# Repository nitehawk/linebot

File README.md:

linebot
=======

Simple Line following robot

This design is based on a design at http://playwithrobots.com/make-it-form-scratch/simple-line-follower-robot
I have switched the sensor modules to use IR LEDs and IR Photodiodes instead of basic white LEDs.
Schematics capture was originally done in KiCad.   Rebuilt as v2 in diptrace.

Boards can be ordered from OshPark:
v1 board: http://www.oshpark.com/shared_projects/IUjxxEeG
v2 main board:  http://www.oshpark.com/shared_projects/y54Hc1CZ
v2 sensor board:  http://www.oshpark.com/shared_projects/1NccGd6E

I will be developing a model for the chassis for the v1 electronics printable in a 3D printer.

Status:
========

I have ordered a set of v1 electronics from Oshpark.   Chassis design will start after the boards and parts arrive and are tested.

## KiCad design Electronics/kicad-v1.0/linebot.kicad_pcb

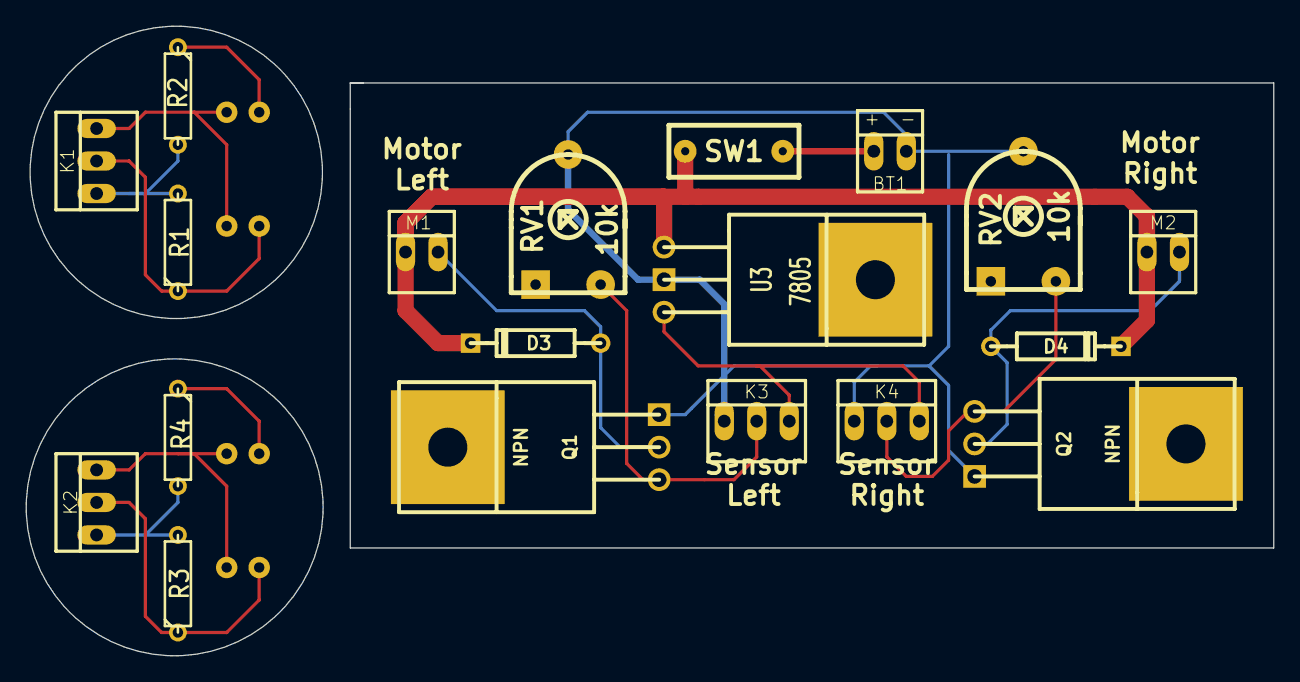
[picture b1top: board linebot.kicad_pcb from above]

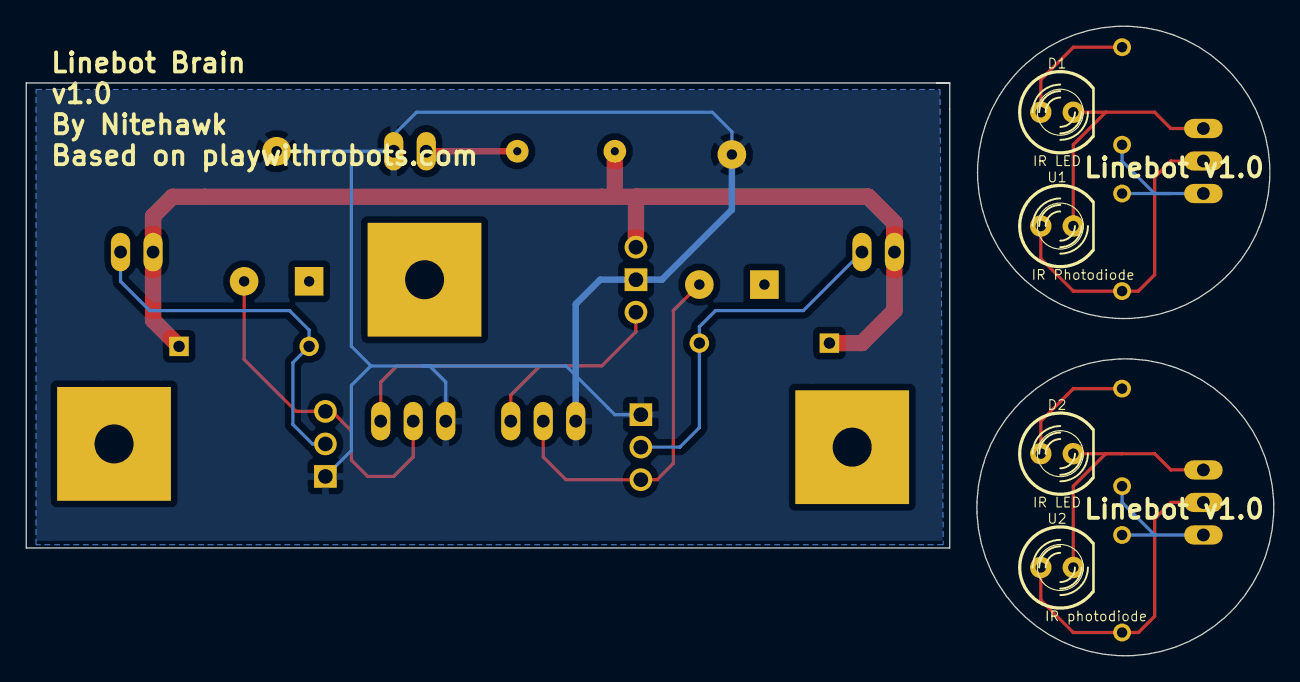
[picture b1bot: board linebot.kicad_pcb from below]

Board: 2 copper layers, 97.4 x 49.2 mm, 23 parts (4 on the bottom side), 16 nets.

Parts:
BT1: + -; PINHEAD1-2
D1, D2: IR LED; LED-5MM
D3, D4: DO-41
K1, K2, K3, K4: PINHEAD1-3
M1, M2: PINHEAD1-2
Q1, Q2: NPN; TO220
R1, R3: 10k; R3
R2: R3
R4: 100; R3
RV1, RV2: 10k; POACCH
SW1: DIPS-DS01
U1: IR Photodiode; LED-5MM
U2: IR photodiode; LED-5MM
U3: 7805; LM78XX

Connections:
5V: K3.3, K4.3, U3.VO
9V: D3.2, D4.2, M1.1, M2.1, SW1.2, U3.VI
GND: BT1.2, K3.1, K4.1, Q1.1, Q2.1, RV1.2, RV2.2, U3.GND
unnamed: K3.2, Q1.2, RV1.3
unnamed: D3.1, M1.2, Q1.3
unnamed: K4.2, Q2.2, RV2.3
unnamed: D1.2, K1.3, U1.2
unnamed: D4.1, M2.2, Q2.3
unnamed: BT1.1, SW1.1
unnamed: K1.1, R1.2, R2.2
unnamed: D1.1, R2.1
unnamed: K2.2, R3.1, U2.1
unnamed: D2.2, K2.3, U2.2
unnamed: K2.1, R3.2, R4.2
unnamed: D2.1, R4.1
unnamed: K1.2, R1.1, U1.1

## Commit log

2014-01-05 Update Readme
    Basic description of the project
2014-01-05 Add original kicad capture of circuit to project
2014-01-05 Additional tweaks regarding electronics
2014-01-06 Rebuild boards in diptrace
2014-01-06 Tweak and generate gerbers.
2014-01-06 Update Readme
    Add links to boards on oshpark. Update current status.
2014-01-06 Ignore gerber zips
2014-01-06 Tweak ignore
